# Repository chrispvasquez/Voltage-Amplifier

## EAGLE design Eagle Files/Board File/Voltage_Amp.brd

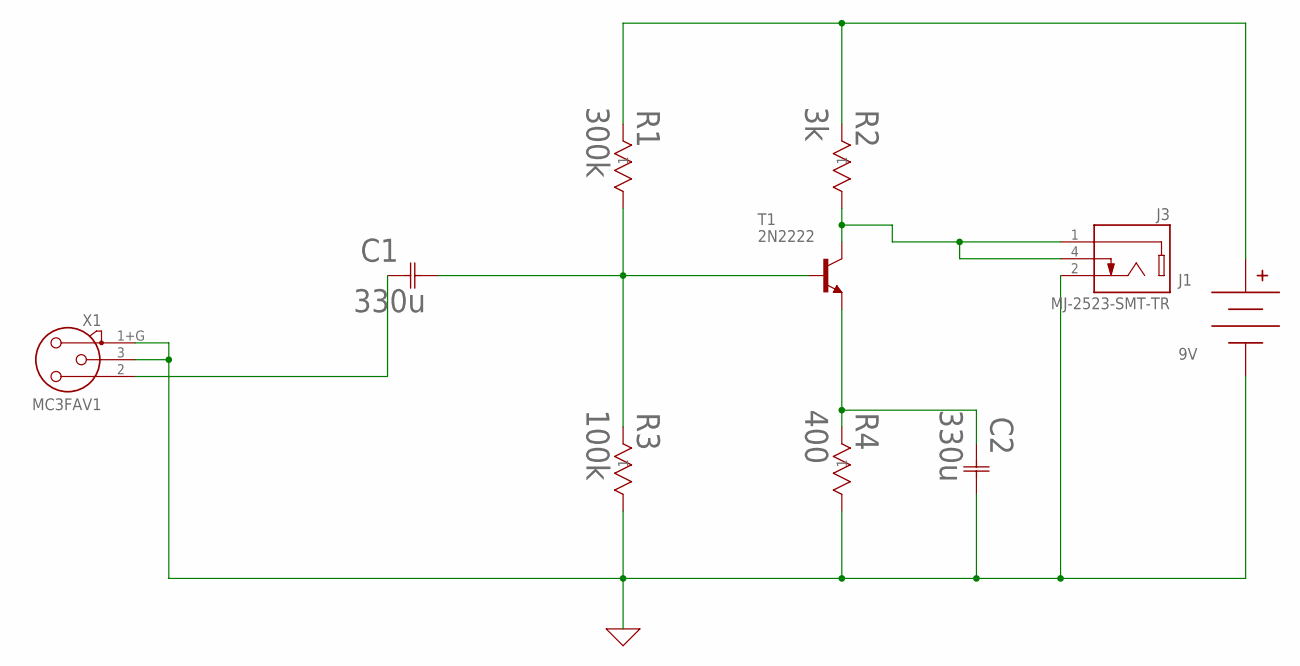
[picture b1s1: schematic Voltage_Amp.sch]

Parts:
C1, C2: 330u; U1-Z_NCH
J1: 9V; BC9VPC
J3: MJ-2523-SMT-TR
R1: 300k; CMF55
R2: 3k; CMF55
R3: 100k; CMF55
R4: 400; CMF55
T1: 2N2222; TO18
X1: MC3FAV1; NC3FAV1

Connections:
0: C2.2, J1.V-, J3.2 (TIP), R3.2, R4.2, X1.1+G (1), X1.3
unnamed: C1.2, R1.2, R3.1, T1.2 (B)
unnamed: J1.V+, R1.1, R2.1
unnamed: J3.1 (SLEEVE), J3.4 (TIP_SWITCH), R2.2, T1.3 (C)
unnamed: C2.1, R4.1, T1.1 (E)
unnamed: C1.1, X1.2

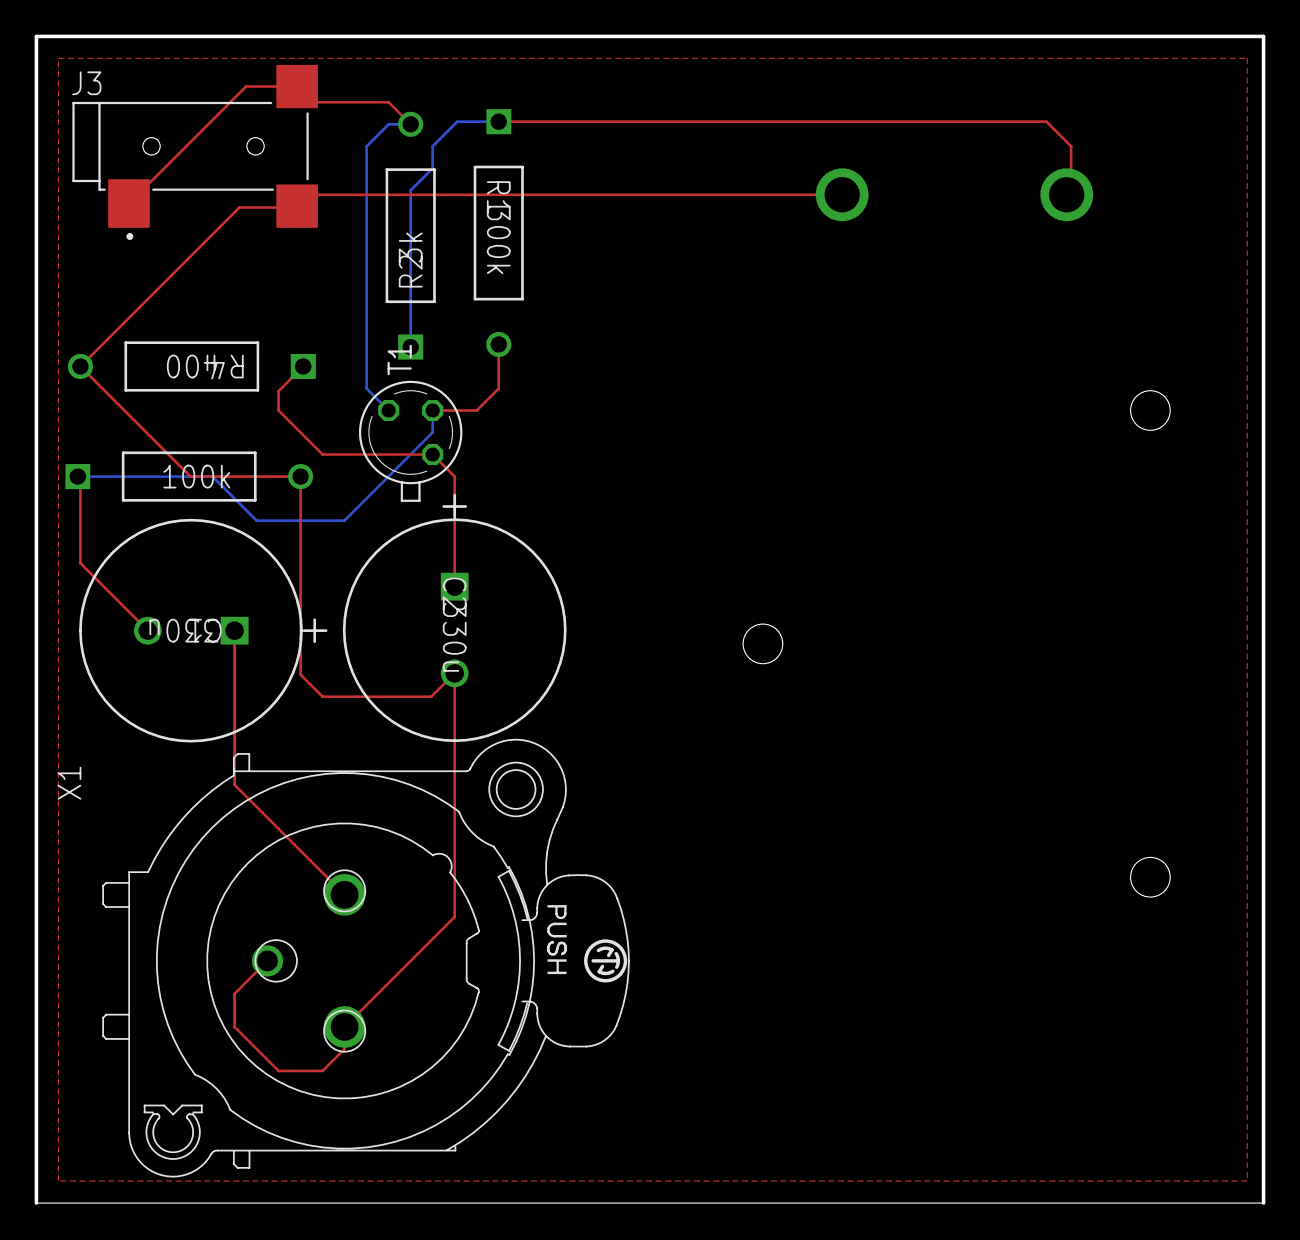
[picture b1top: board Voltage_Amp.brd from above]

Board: 2 copper layers, 70.8 x 67.3 mm, 10 parts (1 on the bottom side), 6 nets.

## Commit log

2022-10-01 Uploading to GitHub

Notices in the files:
parts and their libraries:
SparkFun-Connectors: Licensing: Creative Commons ShareAlike 4.0 International - https://creativecommons.org/licenses/by-sa/4.0
